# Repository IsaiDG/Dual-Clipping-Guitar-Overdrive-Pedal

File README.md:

# Dual-Clipping-Guitar-Overdrive-Pedal

## Overview
This pedal was based on Wampler Pedals' guitar overdrive circuit. It builds on the Walpler's diode clipping mechanism within the feedback loop of a TL082 op amp by adding a switchable hard clipping path outside of the opamp. This switching is done with a Triple Pole Double Throw (3PDT) footswitch with one pole illuminating an LED to indicate which switching mode is active.

The reason for the creation of this pedal was to learn AC analysis and design techniques before being officially taught these skills in my college courses. Also my current overdrive pedal broke so I needed a new one. Valueable technical skills were also learned in the creation of this pedal including software simulation through LTSpice, breadboarding, PCB design through KiCad, and soldering. 

## Concepts Learned and Applied
 - Diode Clipping (1N4148) within TL082 op amp feedback loop (Soft Clipping)
 - Diode Clipping after feedback loop (Hard Clippling)
 - Variable op amp gain
 - High/Low Pass filters
 - Coupling and Decoupling capacitors
 - DC bias
 - Variable tone control
 - Variable Volume control
 - 3PDT switching
 - Op amp Gain Bandwidth Product (GBP)

## Design and Devlopment Process
1. Circuit Design and Simulation: Developed and analyzed clipping circuits seperately in LTspice to investigate signal behavior. Imported real guitar files to see how circuit aurally affected real audio

2. Breadboard Prototyping: Realized circuit onto breadboard and verified bias voltage by comparing simulated behavior and multimeter readings. Troubleshooted issues including incorrect input and output terminals, uneven feedback loop voltages, and faulty components.

3. PCB Design: Full schematic made in KiCAD using 3PDT switch. Created custom footprints for switch and potentiometers. Created PCB design and prepared the design for fabrication
 
4. Hardware Assembly (In Progress): Solder parts onto custom PCB

## Future Projects
As my first independent analog electronics project, this pedal established a foundation for more advanced hardware design. Future projects will build on these skills through more complex analog circuits, embedded systems, and digital signal processing. Potential improvements could include cleaning up the PCB layout, creating pedal case, and adding a bypass switching capability.

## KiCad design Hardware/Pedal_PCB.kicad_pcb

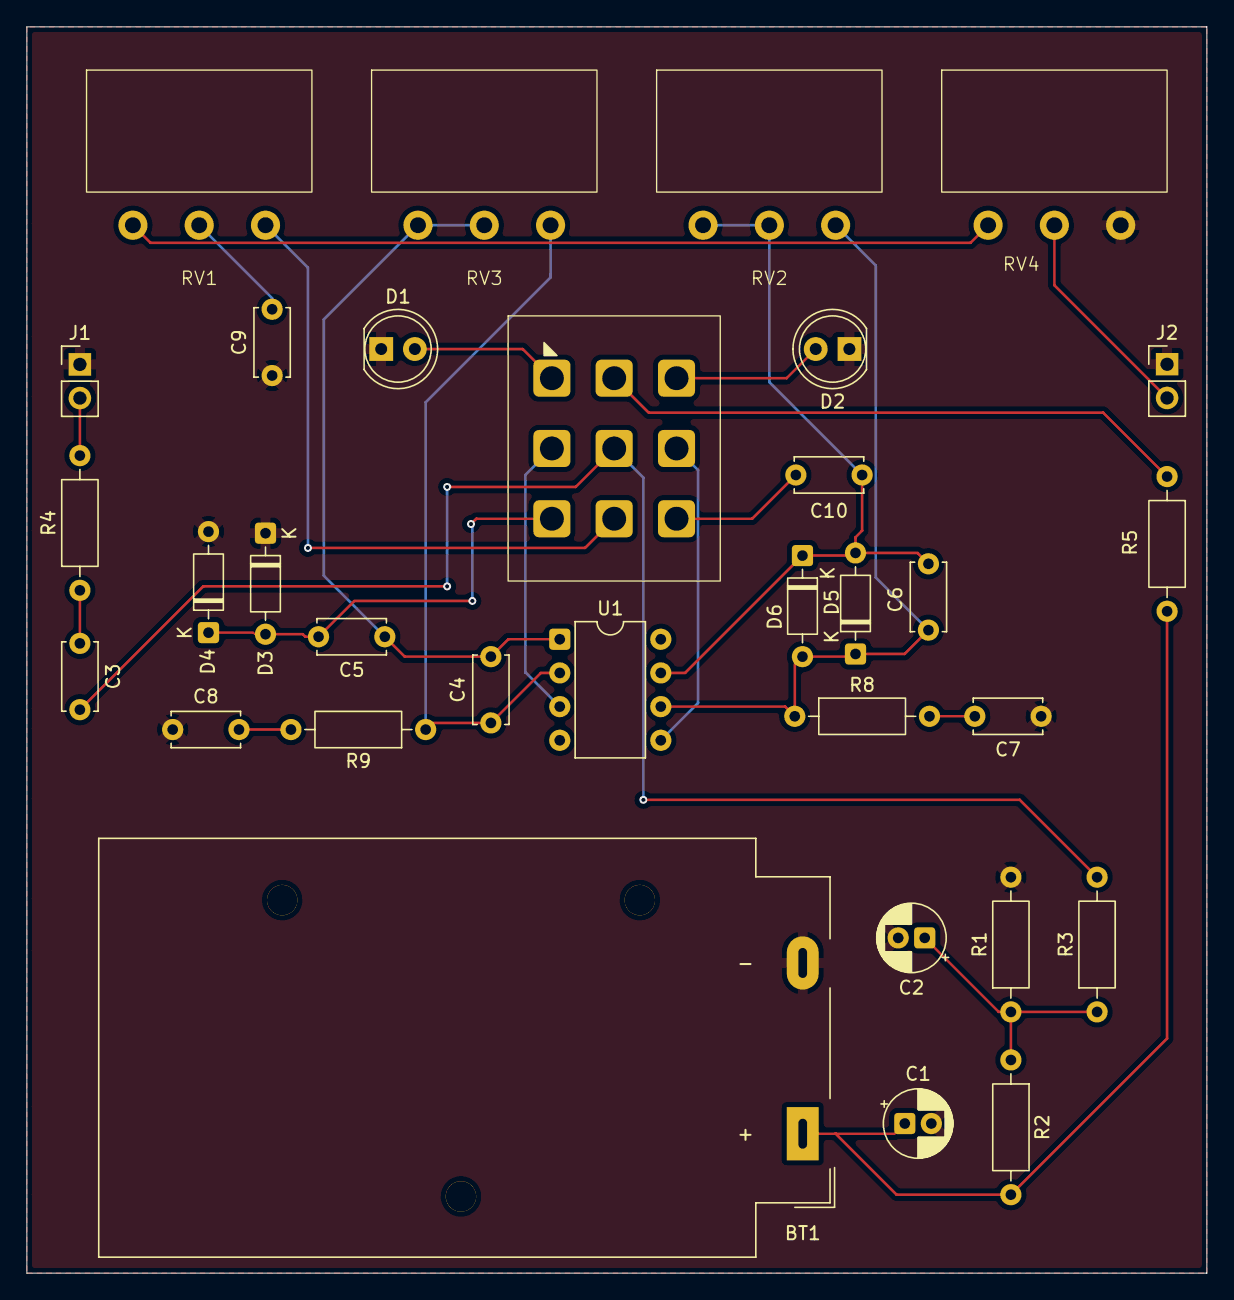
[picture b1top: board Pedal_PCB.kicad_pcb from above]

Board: 4 copper layers, 89.0 x 94.0 mm, 32 parts (0 on the bottom side), 23 nets.

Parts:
BT1: 9V; BatteryHolder_MPD_BA9VPC_1xPP3
C1, C2: 100u; CP_Radial_D5.0mm_P2.00mm
C3: 470n; C_Disc_D5.0mm_W2.5mm_P5.00mm
C4, C6: 100p; C_Disc_D5.0mm_W2.5mm_P5.00mm
C5, C10: 1u; C_Disc_D5.0mm_W2.5mm_P5.00mm
C7, C8: 220n; C_Disc_D5.0mm_W2.5mm_P5.00mm
C9: 22n; C_Disc_D5.0mm_W2.5mm_P5.00mm
D1, D2: LED; LED_D5.0mm
D3, D4, D5, D6: 1N4148; D_DO-35_SOD27_P7.62mm_Horizontal
J1, J2: AudioJack2; PinHeader_1x02_P2.54mm_Vertical
R1, R2, R4: 10k; R_Axial_DIN0207_L6.3mm_D2.5mm_P10.16mm_Horizontal
R3: 1M; R_Axial_DIN0207_L6.3mm_D2.5mm_P10.16mm_Horizontal
R5: 330; R_Axial_DIN0207_L6.3mm_D2.5mm_P10.16mm_Horizontal
R8, R9: 1k; R_Axial_DIN0207_L6.3mm_D2.5mm_P10.16mm_Horizontal
RV1: 10k; pots
RV2, RV3: 500k; pots
RV4: 100k; pots
SW1A1: SW_SPDT; 3PDT_FootPrint
U1: TL082; DIP-8_W7.62mm

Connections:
GND: BT1.2 (-), C1.2, C2.2, C7.1, C8.1, C9.1, D1.1 (K), D2.1 (K), D3.1 (K), D4.2 (A), J1.1, J2.1, R1.2, RV4.3
unnamed: BT1.1 (+), C1.1, R2.2, R5.2
unnamed: C2.1, R1.1, R2.1, R3.1
unnamed: C3.1, R4.1
unnamed: C4.2, C5.1, RV3.1, RV3.2, U1.1
unnamed: C7.2, R8.2
unnamed: C8.2, R9.2
unnamed: C9.2, RV1.2
unnamed: D1.2 (A), SW1A1.1 (A)
unnamed: D2.2 (A), SW1A1.3 (C)
unnamed: C5.2, D3.2 (A), D4.1 (K), SW1A1.7
unnamed: C6.2, C10.1, D5.2 (A), D6.1 (K), RV2.1, RV2.2, U1.7
unnamed: C6.1, D5.1 (K), D6.2 (A), R8.1, RV2.3, U1.6 (-)
unnamed: J1.2, R4.2
unnamed: J2.2, RV4.2
unnamed: RV1.1, RV4.1
unnamed: R5.1, SW1A1.2 (B)
unnamed: SW1A1.4, U1.3 (+)
unnamed: C3.2, R3.2, SW1A1.5
unnamed: SW1A1.6, U1.5 (+)
unnamed: RV1.3, SW1A1.8
unnamed: C10.2, SW1A1.9
unnamed: C4.1, R9.1, RV3.3, U1.2 (-)
